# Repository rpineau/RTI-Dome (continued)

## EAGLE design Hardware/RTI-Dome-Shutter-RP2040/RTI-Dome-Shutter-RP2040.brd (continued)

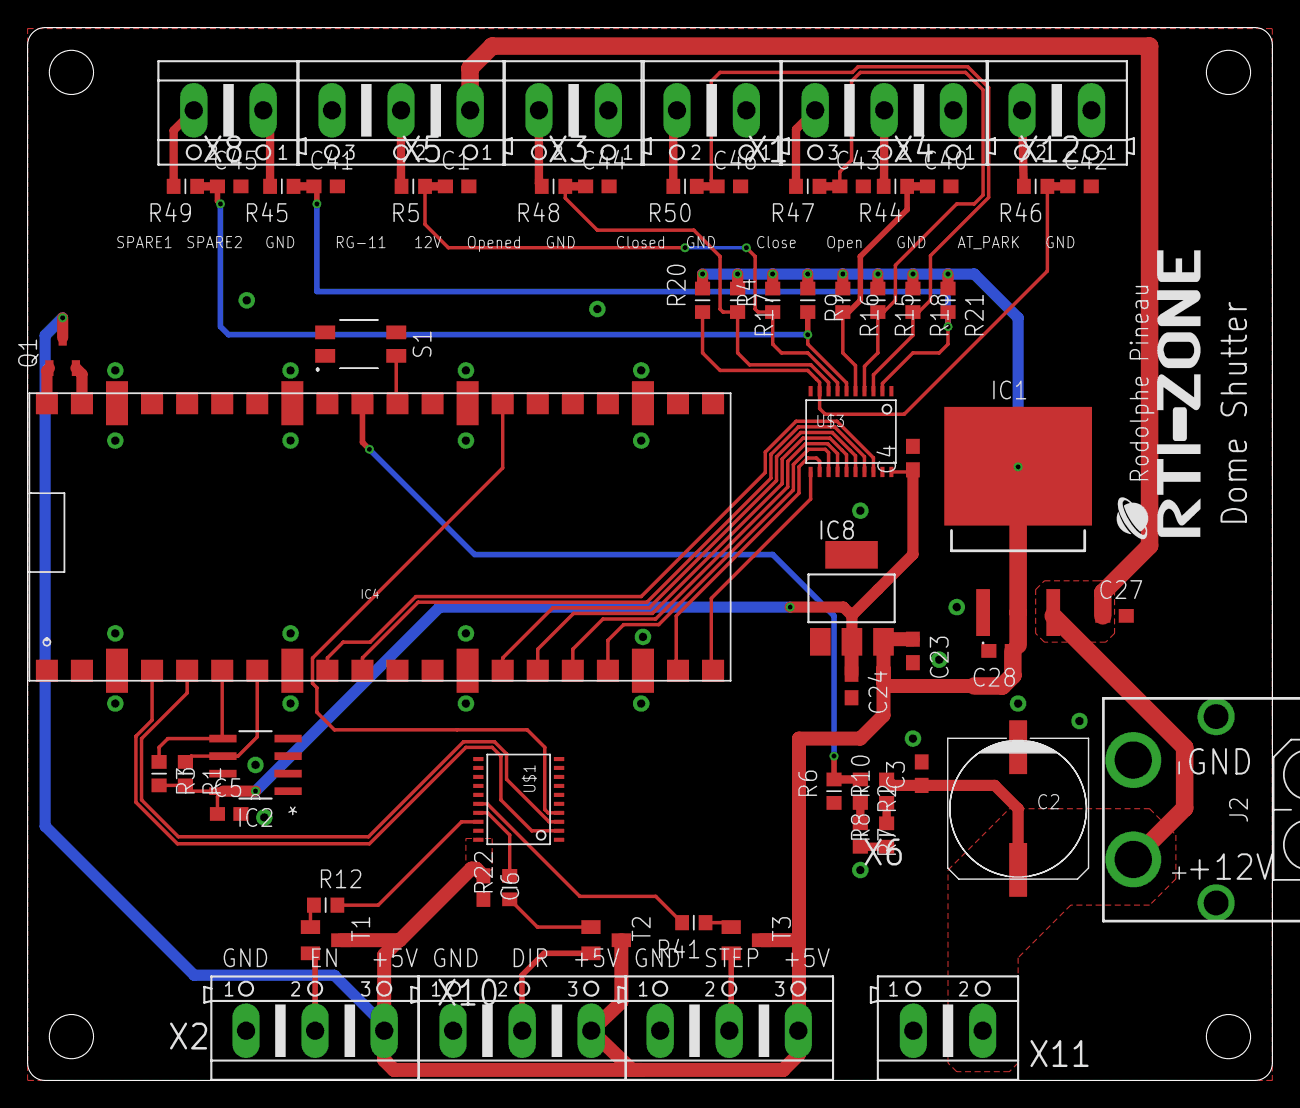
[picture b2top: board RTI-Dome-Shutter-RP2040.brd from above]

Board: 2 copper layers, 90.2 x 76.3 mm, 66 parts (0 on the bottom side), 49 nets.

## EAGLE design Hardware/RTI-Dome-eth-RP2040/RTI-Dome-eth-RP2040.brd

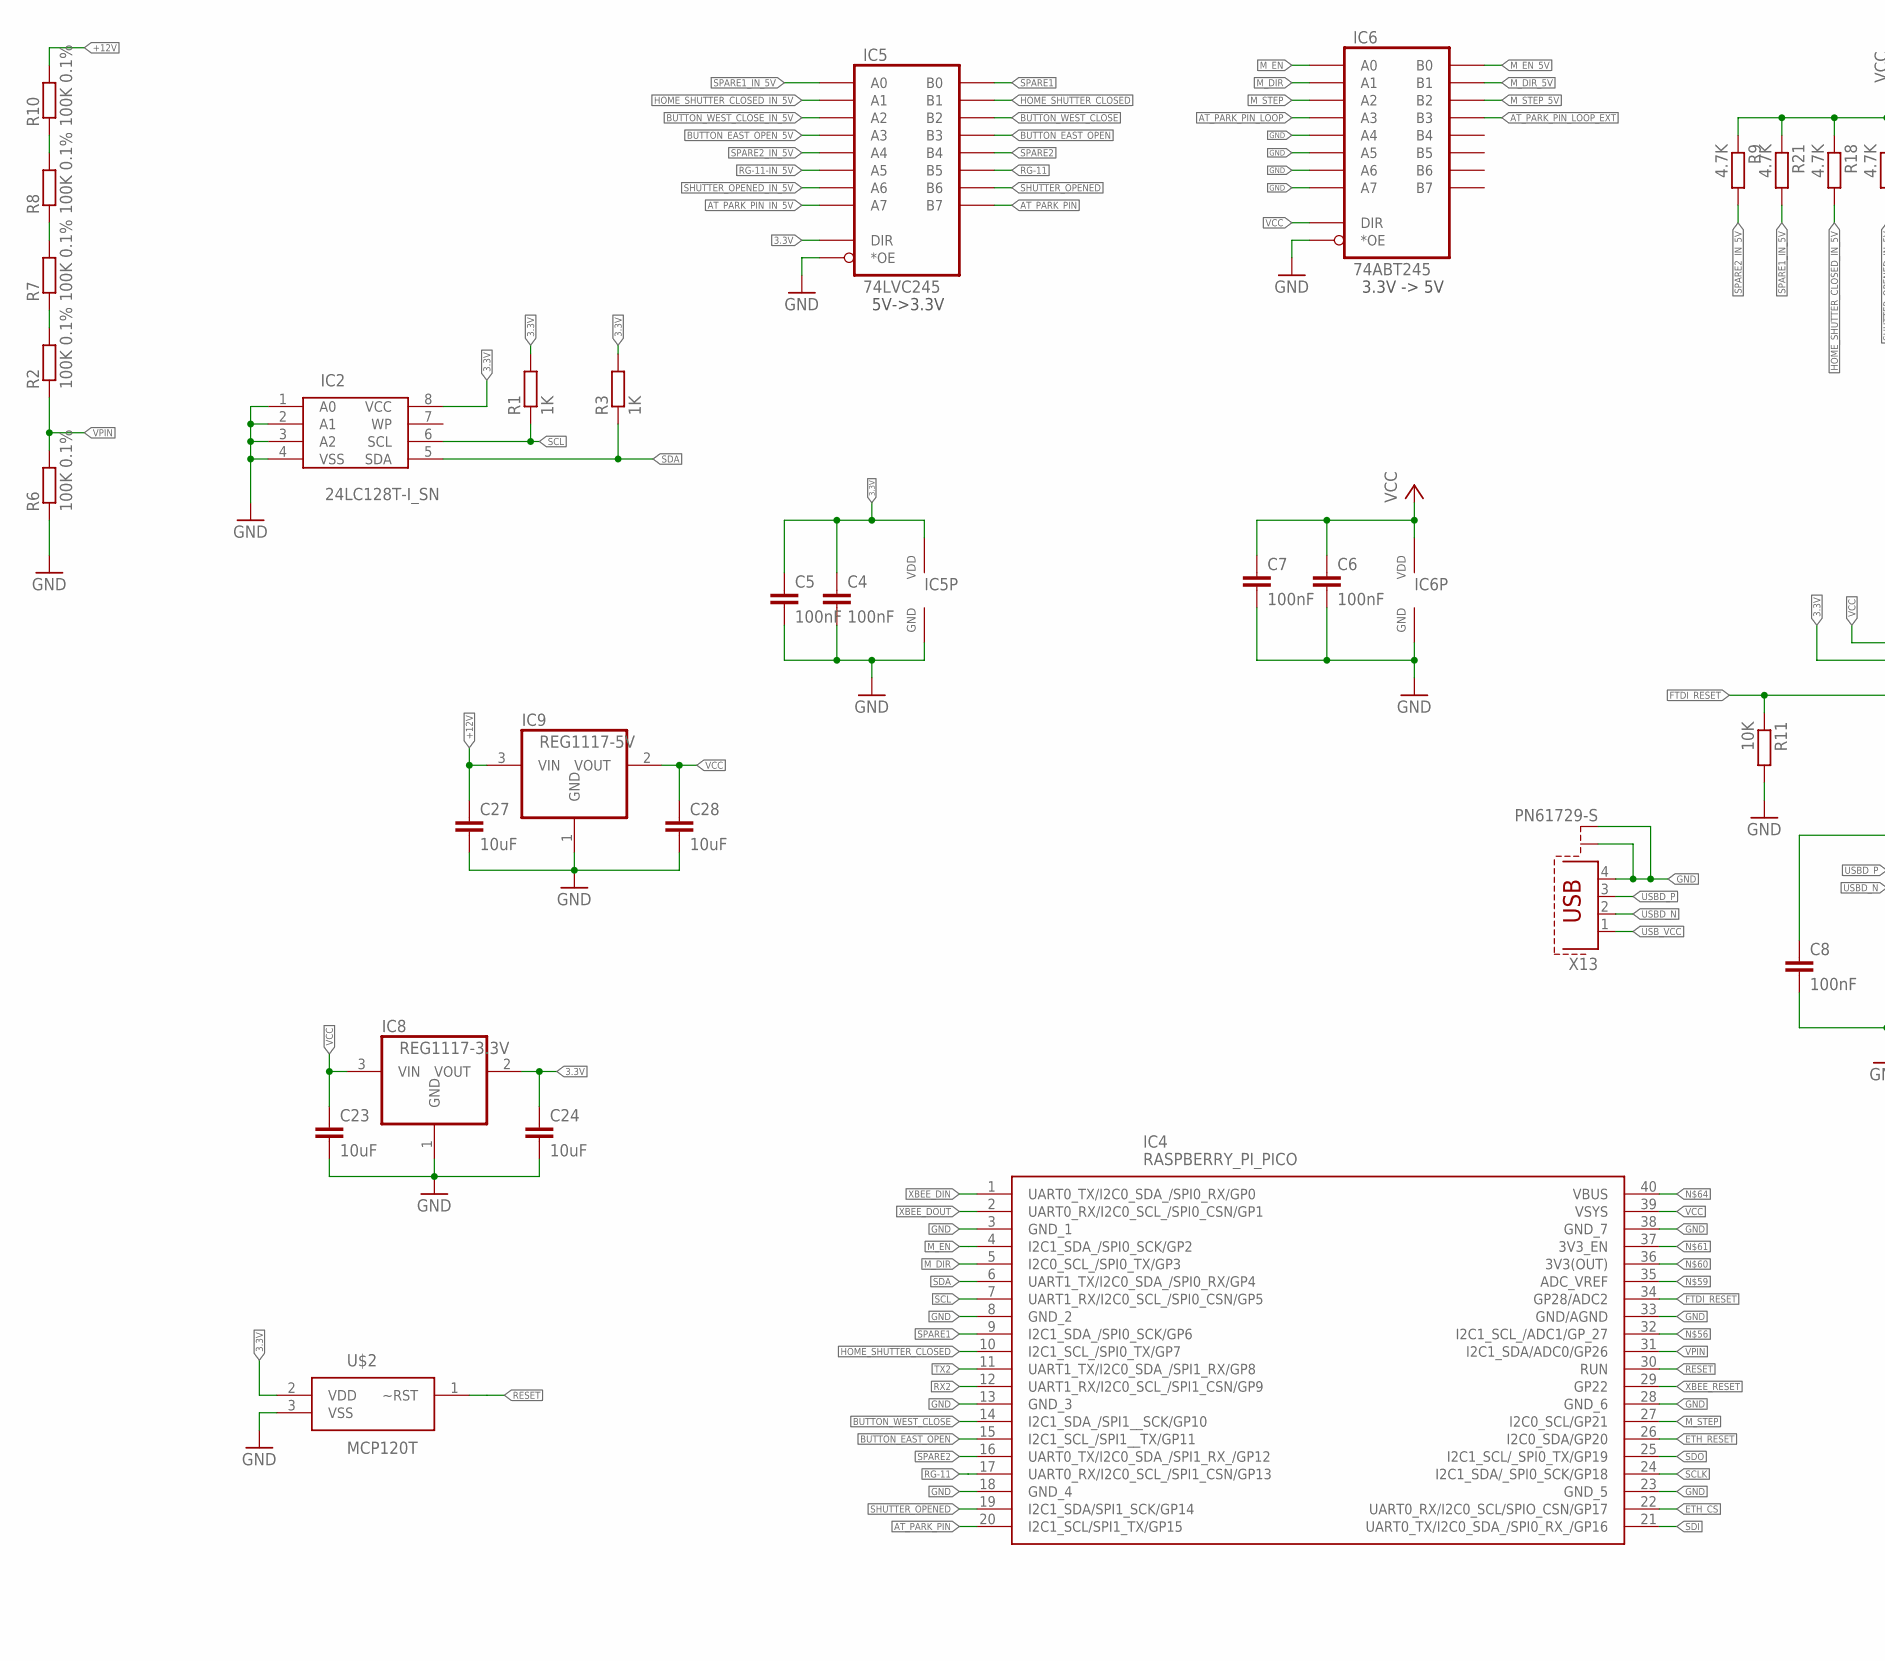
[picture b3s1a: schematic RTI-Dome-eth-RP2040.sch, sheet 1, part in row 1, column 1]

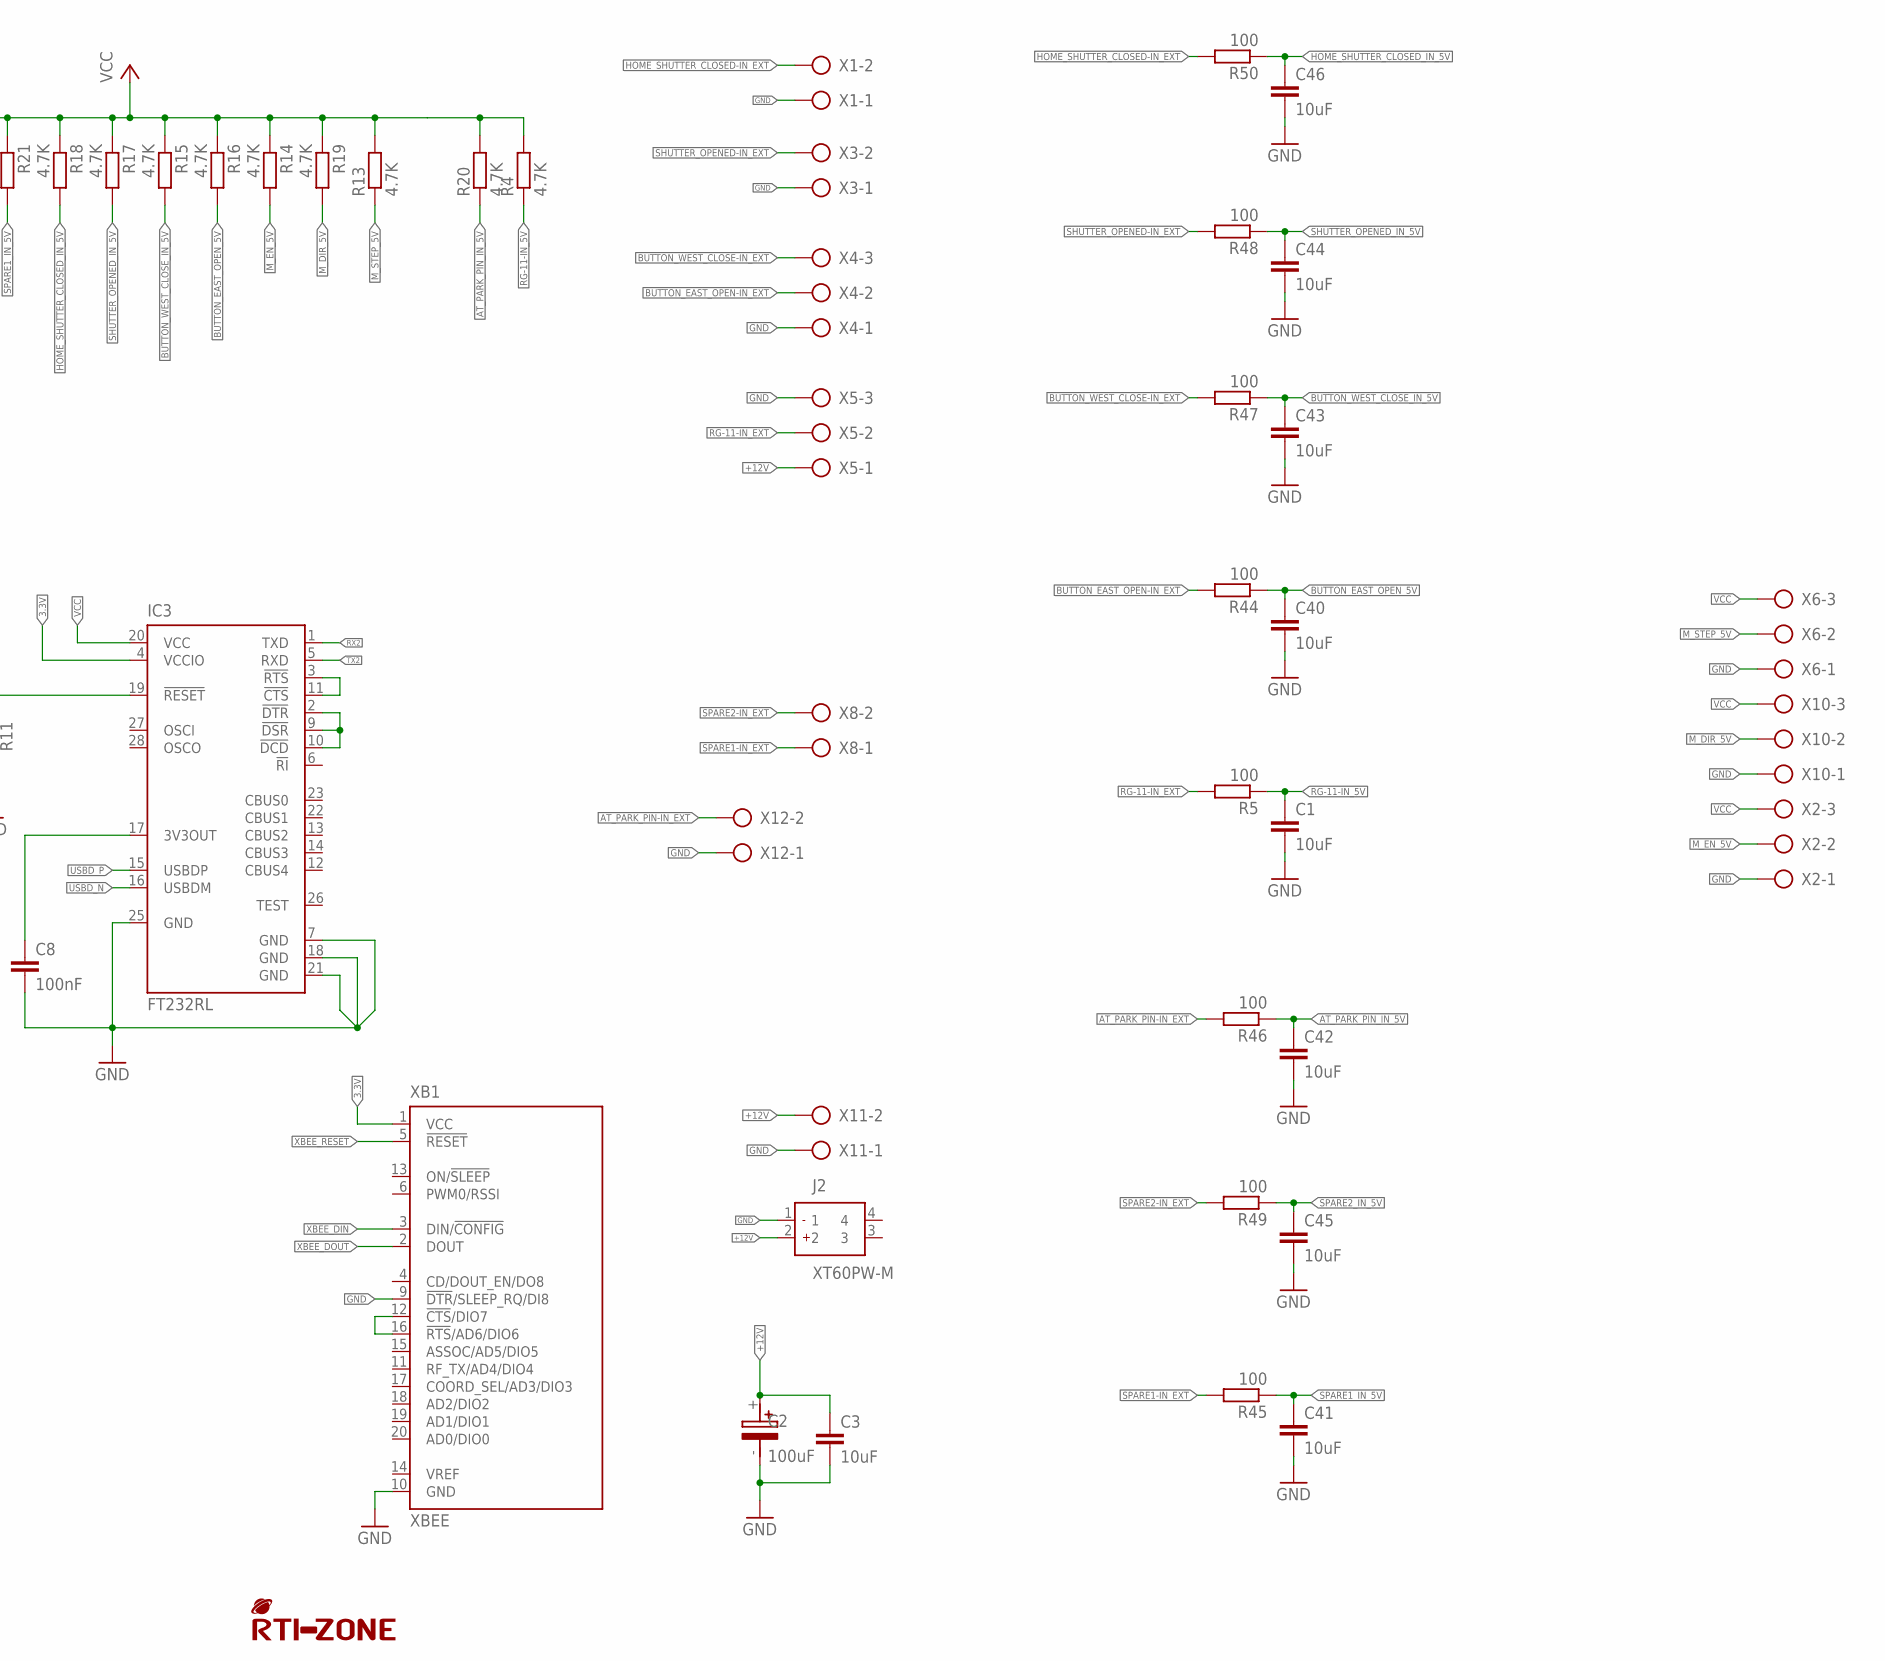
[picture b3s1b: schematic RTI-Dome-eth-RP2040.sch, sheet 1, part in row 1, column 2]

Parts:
C1, C3, C23, C24, C27, C28, C40, C41, C42, C43, C44, C45, C46: 10uF; C0805; MPN CC0805KKX5R8BB106
C2: 100uF; UD-10X10_NICHICON; MPN MAL215099804E3
C4, C5, C6, C7, C8: 100nF; C0805; MPN 0805YD104KAT2A
IC2: 24LC128T-I_SN; SOIC127P600X175-8N
IC3: FT232RL; SSOP28; MPN FT232RL-REEL
IC4: RASPBERRY_PI_PICO; RASPBERRYPIPICO; MANUFACTURER_PART_NUMBER SC0916; MOUSER_PART_NUMBER SC0915
IC5: 74LVC245; TSSOP20
IC6: 74ABT245; TSSOP20
IC8: REG1117-3.3V; SOT223; MPN REG1117-3.3/2K5
IC9: REG1117-5V; SOT223; MPN REG1117-3.3/2K5
J2: XT60PW-M; XT60PWM
R1, R3: 1K; R0805; MPN RT0805FRE071KL
R2, R6, R7, R8, R10: 100K 0.1%; R0805; MPN AT0805BRD07100KL
R4, R9, R13, R14, R15, R16, R17, R18, R19, R20, R21: 4.7K; R0805; MPN RT0805FRE074K7L
R5, R44, R45, R46, R47, R48, R49, R50: 100; R0805; MPN RT0805FRD07100RL
R11: 10K; R0805; MPN RT0805FRE0710KL
U$2: MCP120T; SOT95P237X112-3N; MPN MCP120T-270I/TT
U$4: RTI-LOGO_BIG; LOGO_BIG
X1, X3, X8, X11, X12: AK500/2; MPN 691101710002
X2, X6, X10: AK500/3
X4, X5: AK500/3; MPN 691101710003
X13: PN61729-S; MPN SS-52300-001
XB1: XBEE

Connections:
3.3V: C4.1, C5.1, C24.1, IC2.8 (VCC), IC3.4 (VCCIO), IC5.P$1 (DIR), IC5.P$20 (VDD), IC8.2 (VOUT), R1.2, R3.2, U$2.2 (VDD), XB1.1 (VCC); also elsewhere on the board
+12V: C2.+, C3.1, C27.1, IC9.3 (VIN), J2.2, R10.2, X5.1, X11.2
AT_PARK_PIN: IC4.20 (I2C1_SCL/SPI1_TX/GP15), IC5.P$11 (B7)
AT_PARK_PIN-IN_EXT: R46.2, X12.2
AT_PARK_PIN_IN_5V: C42.1, IC5.P$9 (A7), R20.1, R46.1
AT_PARK_PIN_LOOP: IC6.P$5 (A3)
AT_PARK_PIN_LOOP_EXT: IC6.P$15 (B3)
BUTTON_EAST_OPEN: IC4.15 (I2C1_SCL_/SPI1__TX/GP11), IC5.P$15 (B3)
BUTTON_EAST_OPEN-IN_EXT: R44.2, X4.2
BUTTON_EAST_OPEN_5V: C40.1, IC5.P$5 (A3), R16.2, R44.1
BUTTON_WEST_CLOSE: IC4.14 (I2C1_SDA_/SPI1__SCK/GP10), IC5.P$16 (B2)
BUTTON_WEST_CLOSE-IN_EXT: R47.2, X4.3
BUTTON_WEST_CLOSE_IN_5V: C43.1, IC5.P$4 (A2), R15.2, R47.1
DTR_DSR_DCD: IC3.2 (!DTR), IC3.9 (!DSR), IC3.10 (!DCD)
ETH_CS: IC4.22 (UART0_RX/I2C0_SCL/SPIO_CSN/GP17); also elsewhere on the board
ETH_RESET: IC4.26 (I2C0_SDA/GP20); also elsewhere on the board
FTDI_RESET: IC3.19 (!RESET), IC4.34 (GP28/ADC2), R11.1
GND: C1.2, C2.-, C3.2, C4.2, C5.2, C6.2, C7.2, C8.2, C23.2, C24.2, C27.2, C28.2, C40.2, C41.2, C42.2, C43.2, C44.2, C45.2, C46.2, IC2.1 (A0), IC2.2 (A1), IC2.3 (A2), IC2.4 (VSS), IC3.7 (GND), IC3.18 (GND), IC3.21 (GND), IC3.25 (GND), IC4.3 (GND_1), IC4.8 (GND_2), IC4.13 (GND_3), IC4.18 (GND_4), IC4.23 (GND_5), IC4.28 (GND_6), IC4.33 (GND/AGND), IC4.38 (GND_7), IC5.P$10 (GND), IC5.P$19 (*OE), IC6.P$6 (A4), IC6.P$7 (A5), IC6.P$8 (A6), IC6.P$9 (A7), IC6.P$10 (GND), IC6.P$19 (*OE), IC8.1 (GND), IC9.1 (GND), J2.1, R6.1, R11.2, U$2.3 (VSS), X1.1, X2.1, X3.1, X4.1, X5.3, X6.1, X10.1, X11.1, X12.1, X13.4, X13.S1, X13.S2, XB1.9 (!DTR!/SLEEP_RQ/DI8), XB1.10 (GND); also elsewhere on the board
HOME_SHUTTER_CLOSED: IC4.10 (I2C1_SCL_/SPI0_TX/GP7), IC5.P$17 (B1)
HOME_SHUTTER_CLOSED-IN_EXT: R50.2, X1.2
HOME_SHUTTER_CLOSED_IN_5V: C46.1, IC5.P$3 (A1), R18.2, R50.1
M_DIR: IC4.5 (I2C0_SCL_/SPI0_TX/GP3), IC6.P$3 (A1)
M_DIR_5V: IC6.P$17 (B1), R19.2, X10.2
M_EN: IC4.4 (I2C1_SDA_/SPI0_SCK/GP2), IC6.P$2 (A0)
M_EN_5V: IC6.P$18 (B0), R14.2, X2.2
M_STEP: IC4.27 (I2C0_SCL/GP21), IC6.P$4 (A2)
M_STEP_5V: IC6.P$16 (B2), R13.1, X6.2
unnamed: R7.2, R8.1
unnamed: R8.2, R10.1
unnamed: R2.2, R7.1
unnamed: C8.1, IC3.17 (3V3OUT)
unnamed: XB1.12 (!CTS!/DIO7), XB1.16 (!RTS!/AD6/DIO6)
RESET: IC4.30 (RUN), U$2.1 (~RST)
RG-11: IC4.17 (UART0_RX/I2C0_SCL_/SPI1_CSN/GP13), IC5.P$13 (B5)
RG-11-IN_5V: C1.1, IC5.P$7 (A5), R4.1, R5.1
RG-11-IN_EXT: R5.2, X5.2
RTS_CTS: IC3.3 (!RTS), IC3.11 (!CTS)
RX2: IC3.1 (TXD), IC4.12 (UART1_RX/I2C0_SCL_/SPI1_CSN/GP9)
SCL: IC2.6 (SCL), IC4.7 (UART1_RX/I2C0_SCL_/SPI0_CSN/GP5), R1.1
SCLK: IC4.24 (I2C1_SDA/_SPI0_SCK/GP18); also elsewhere on the board
SDA: IC2.5 (SDA), IC4.6 (UART1_TX/I2C0_SDA_/SPI0_RX/GP4), R3.1
SDI: IC4.21 (UART0_TX/I2C0_SDA_/SPI0_RX_/GP16); also elsewhere on the board
SDO: IC4.25 (I2C1_SCL/_SPI0_TX/GP19); also elsewhere on the board
SHUTTER_OPENED: IC4.19 (I2C1_SDA/SPI1_SCK/GP14), IC5.P$12 (B6)
SHUTTER_OPENED-IN_EXT: R48.2, X3.2
SHUTTER_OPENED_IN_5V: C44.1, IC5.P$8 (A6), R17.2, R48.1
SPARE1: IC4.9 (I2C1_SDA_/SPI0_SCK/GP6), IC5.P$18 (B0)
SPARE1-IN_EXT: R45.2, X8.1
SPARE1_IN_5V: C41.1, IC5.P$2 (A0), R21.2, R45.1
SPARE2: IC4.16 (UART0_TX/I2C0_SDA_/SPI1_RX_/GP12), IC5.P$14 (B4)
SPARE2-IN_EXT: R49.2, X8.2
SPARE2_IN_5V: C45.1, IC5.P$6 (A4), R9.2, R49.1
TX2: IC3.5 (RXD), IC4.11 (UART1_TX/I2C0_SDA_/SPI1_RX/GP8)
USBD_N: IC3.16 (USBDM), X13.2
USBD_P: IC3.15 (USBDP), X13.3
USB_VCC: X13.1
VCC: C6.1, C7.1, C23.1, C28.1, IC3.20 (VCC), IC4.39 (VSYS), IC6.P$1 (DIR), IC6.P$20 (VDD), IC8.3 (VIN), IC9.2 (VOUT), R4.2, R9.1, R13.2, R14.1, R15.1, R16.1, R17.1, R18.1, R19.1, R20.2, R21.1, X2.3, X6.3, X10.3
VPIN: IC4.31 (I2C1_SDA/ADC0/GP26), R2.1, R6.2
XBEE_DIN: IC4.1 (UART0_TX/I2C0_SDA_/SPI0_RX/GP0), XB1.3 (DIN/!CONFIG)
XBEE_DOUT: IC4.2 (UART0_RX/I2C0_SCL_/SPI0_CSN/GP1), XB1.2 (DOUT)
XBEE_RESET: IC4.29 (GP22), XB1.5 (!RESET)

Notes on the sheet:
5V->3.3V
3.3V -> 5V

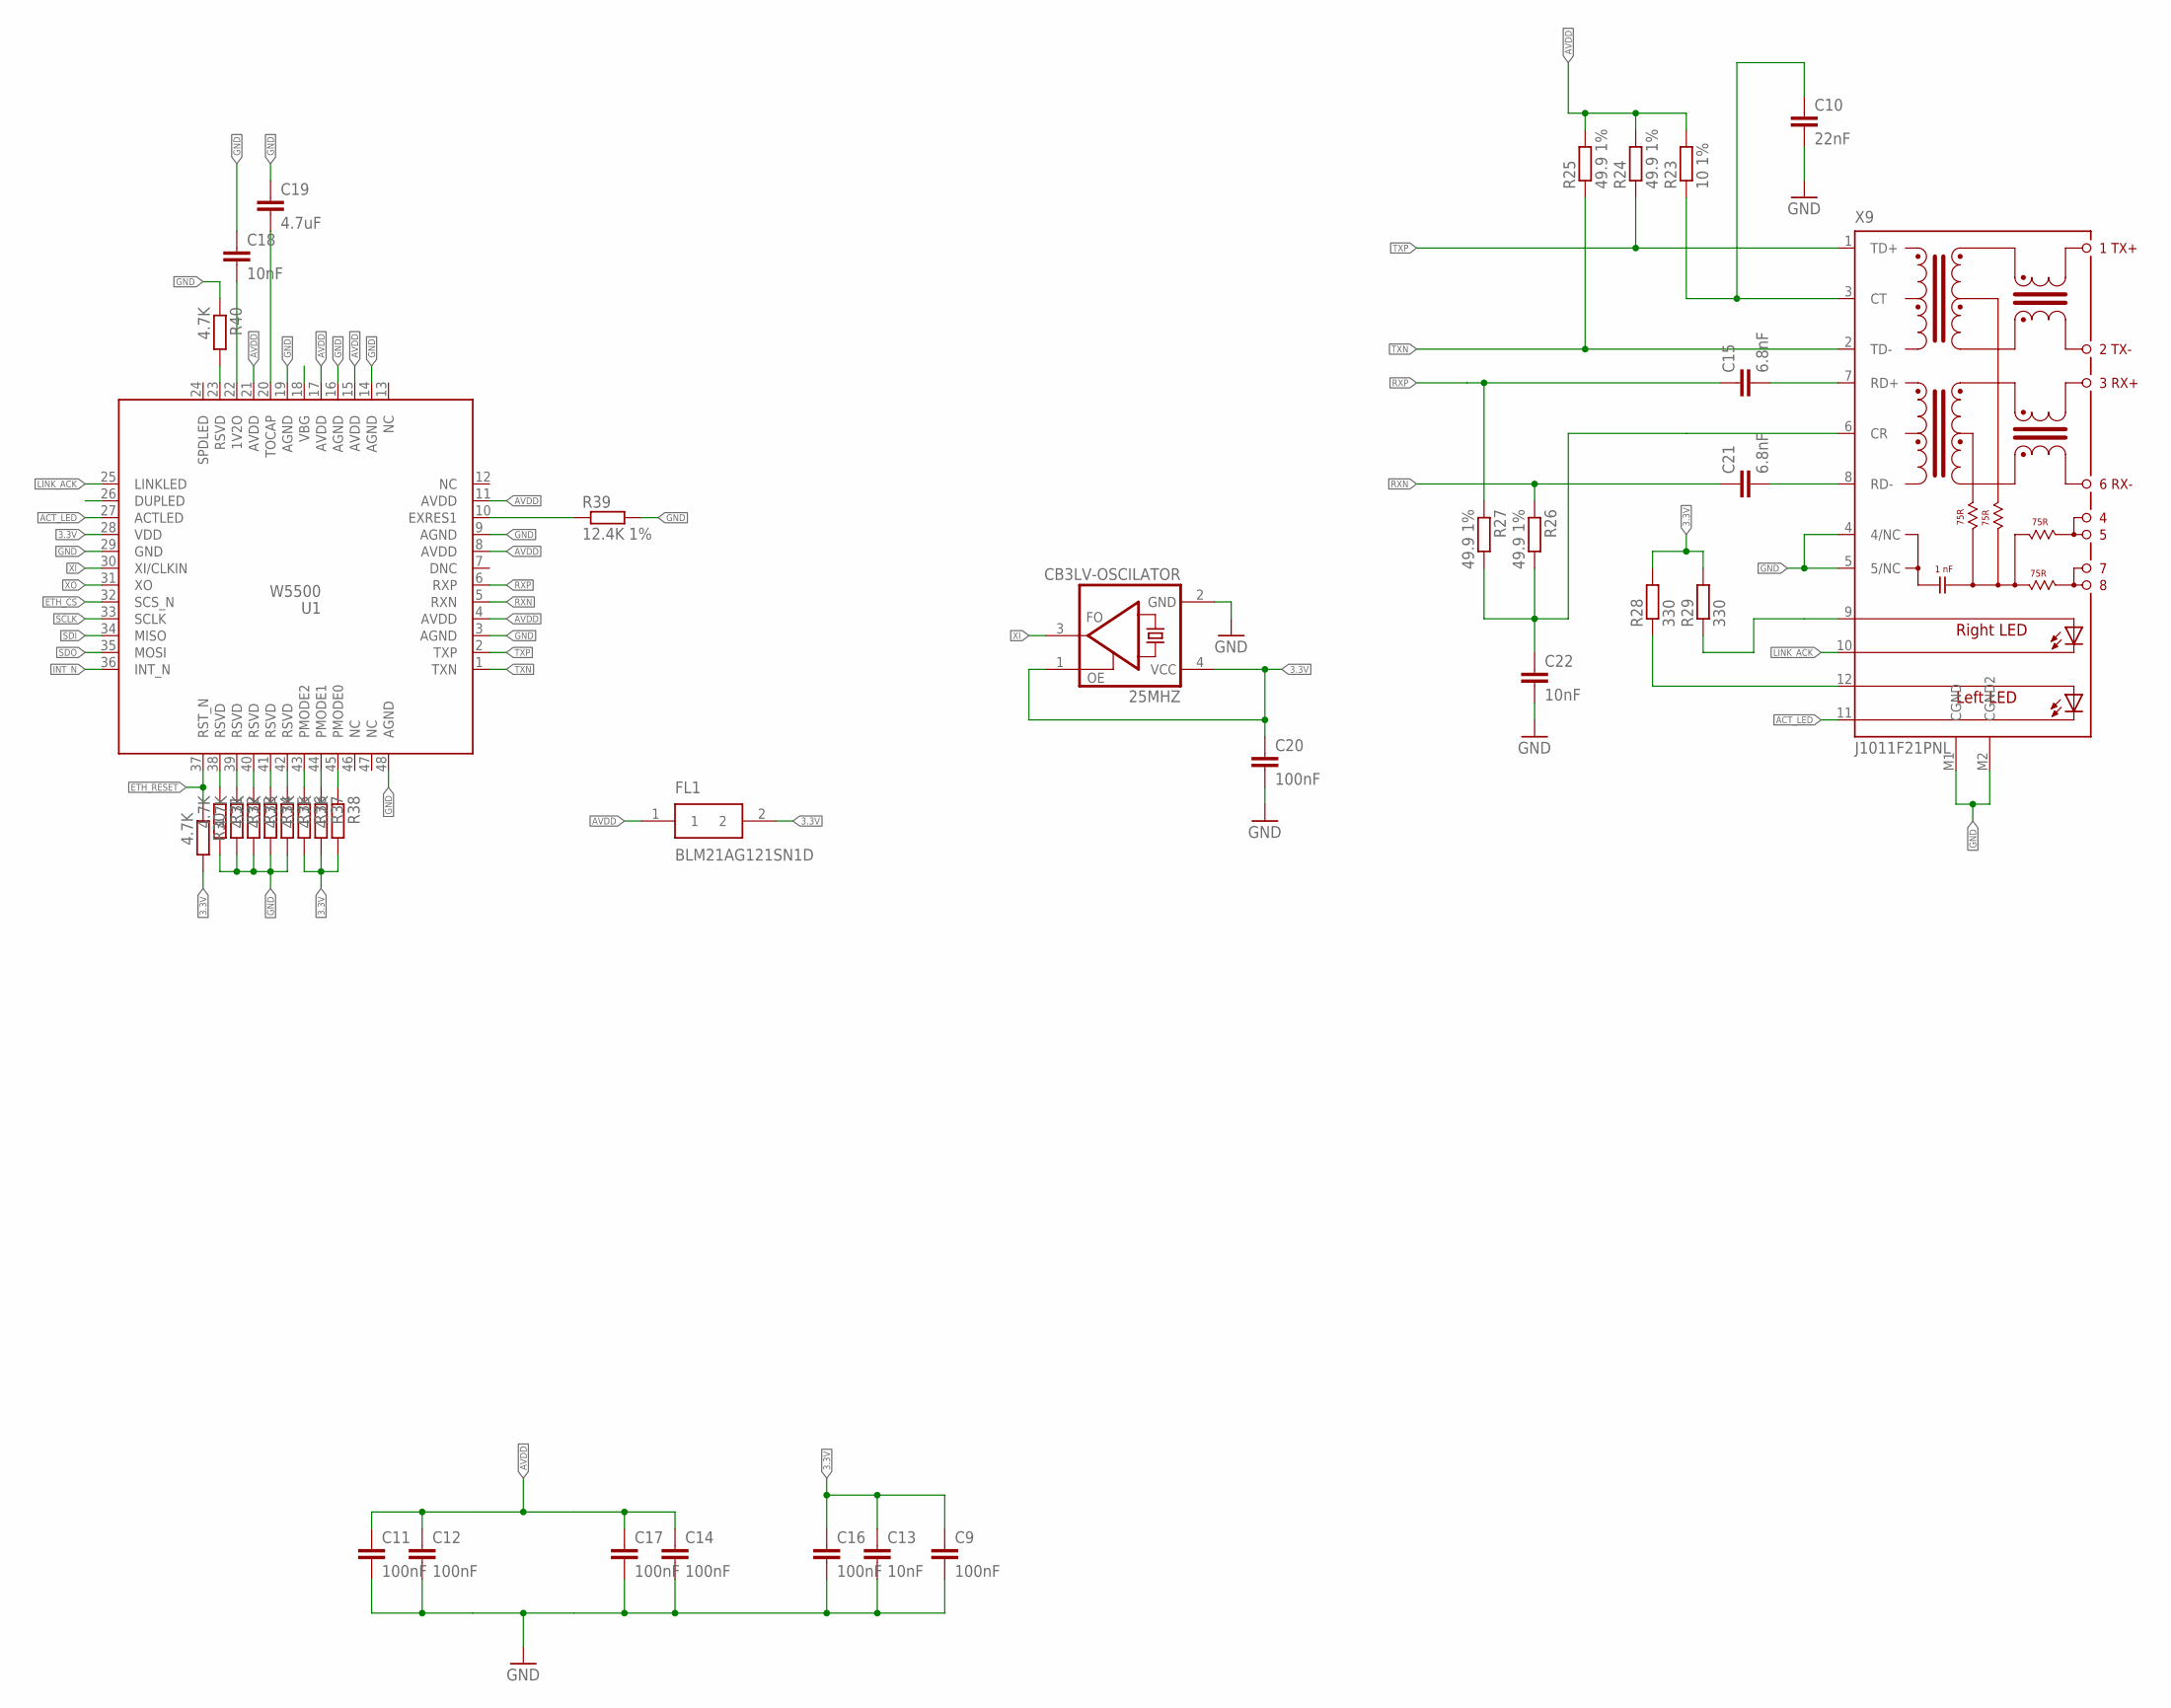
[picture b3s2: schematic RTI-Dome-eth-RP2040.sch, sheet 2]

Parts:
25MHZ: CB3LV-OSCILATOR; SMD-7050_4P; MPN CB3LV-3I-25M0000
C9, C11, C12, C14, C16, C17, C20: 100nF; C0805; MPN 0805YD104KAT2A
C10: 22nF; C0805; MPN CC0805JRX7R8BB223
C13, C18, C22: 10nF; C0805; MPN CC0805KRX7R9BB103
C15, C21: 6.8nF; C0805; MPN C0805C682F4HACTU
C19: 4.7uF; C0805; MPN C0805C475J3RACTU
FL1: BLM21AG121SN1D; L0805; MPN BLM21AG121SN1D
R23: 10 1%; R0805; MPN RT0805FRE1310RL
R24, R25, R26, R27: 49.9 1%; R0805; MPN RC0805FR-0749R9L
R28, R29: 330; R0805; MPN RC0805JR-07330RL
R30, R31, R32, R33, R34, R35, R36, R37, R38, R40: 4.7K; R0805; MPN RT0805FRE074K7L
R39: 12.4K 1%; R0805; MPN RC0805FR-0712K4L
U1: W5500; LQFP48; MPN W5500
X9: J1011F21PNL; MPN J1011F21PNL

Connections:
3.3V: 25MHZ.1 (OE), 25MHZ.4 (VDD), C9.1, C13.1, C16.1, C20.1, FL1.2, R28.2, R29.2, R30.2, R36.2, R37.2, R38.2, U1.28 (VDD); also elsewhere on the board
ACT_LED: U1.27 (ACTLED), X9.11 (C-L)
AVDD: C11.1, C12.1, C14.1, C17.1, FL1.1, R23.2, R24.2, R25.2, U1.4 (AVDD), U1.8 (AVDD), U1.11 (AVDD), U1.15 (AVDD), U1.17 (AVDD), U1.21 (AVDD)
ETH_CS: U1.32 (SCS_N); also elsewhere on the board
ETH_RESET: R30.1, U1.37 (RST_N); also elsewhere on the board
GND: 25MHZ.2 (GND), C9.2, C10.2, C11.2, C12.2, C13.2, C14.2, C16.2, C17.2, C18.1, C19.1, C20.2, C22.2, R31.2, R32.2, R33.2, R34.2, R35.2, R39.2, R40.1, U1.3 (AGND), U1.9 (AGND), U1.14 (AGND), U1.16 (AGND), U1.19 (AGND), U1.29 (GND), U1.48 (AGND), X9.4 (4/NC), X9.5 (5/NC), X9.M1 (CGND), X9.M2 (CGND2); also elsewhere on the board
INT_N: U1.36 (INT_N)
LINK_ACK: U1.25 (LINKLED), X9.10 (C-R)
unnamed: C22.1, R26.2, R27.2, X9.6 (CR)
unnamed: R29.1, X9.9 (A-R)
unnamed: R28.1, X9.12 (AL)
unnamed: C15.2, X9.7 (RD+)
unnamed: C21.2, X9.8 (RD-)
unnamed: C10.1, R23.1, X9.3 (CT)
unnamed: R31.1, U1.38 (RSVD)
unnamed: R32.1, U1.39 (RSVD)
unnamed: R33.1, U1.40 (RSVD)
unnamed: R34.1, U1.41 (RSVD)
unnamed: R35.1, U1.42 (RSVD)
unnamed: R36.1, U1.43 (PMODE2)
unnamed: R37.1, U1.44 (PMODE1)
unnamed: R38.1, U1.45 (PMODE0)
unnamed: C19.2, U1.20 (TOCAP)
unnamed: C18.2, U1.22 (1V2O)
unnamed: R39.1, U1.10 (EXRES1)
unnamed: R40.2, U1.23 (RSVD)
RXN: C21.1, R26.1, U1.5 (RXN)
RXP: C15.1, R27.1, U1.6 (RXP)
SCLK: U1.33 (SCLK); also elsewhere on the board
SDI: U1.34 (MISO); also elsewhere on the board
SDO: U1.35 (MOSI); also elsewhere on the board
TXN: R25.1, U1.1 (TXN), X9.2 (TD-)
TXP: R24.1, U1.2 (TXP), X9.1 (TD+)
XI: 25MHZ.3 (FO), U1.30 (XI/CLKIN)
XO: U1.31 (XO)

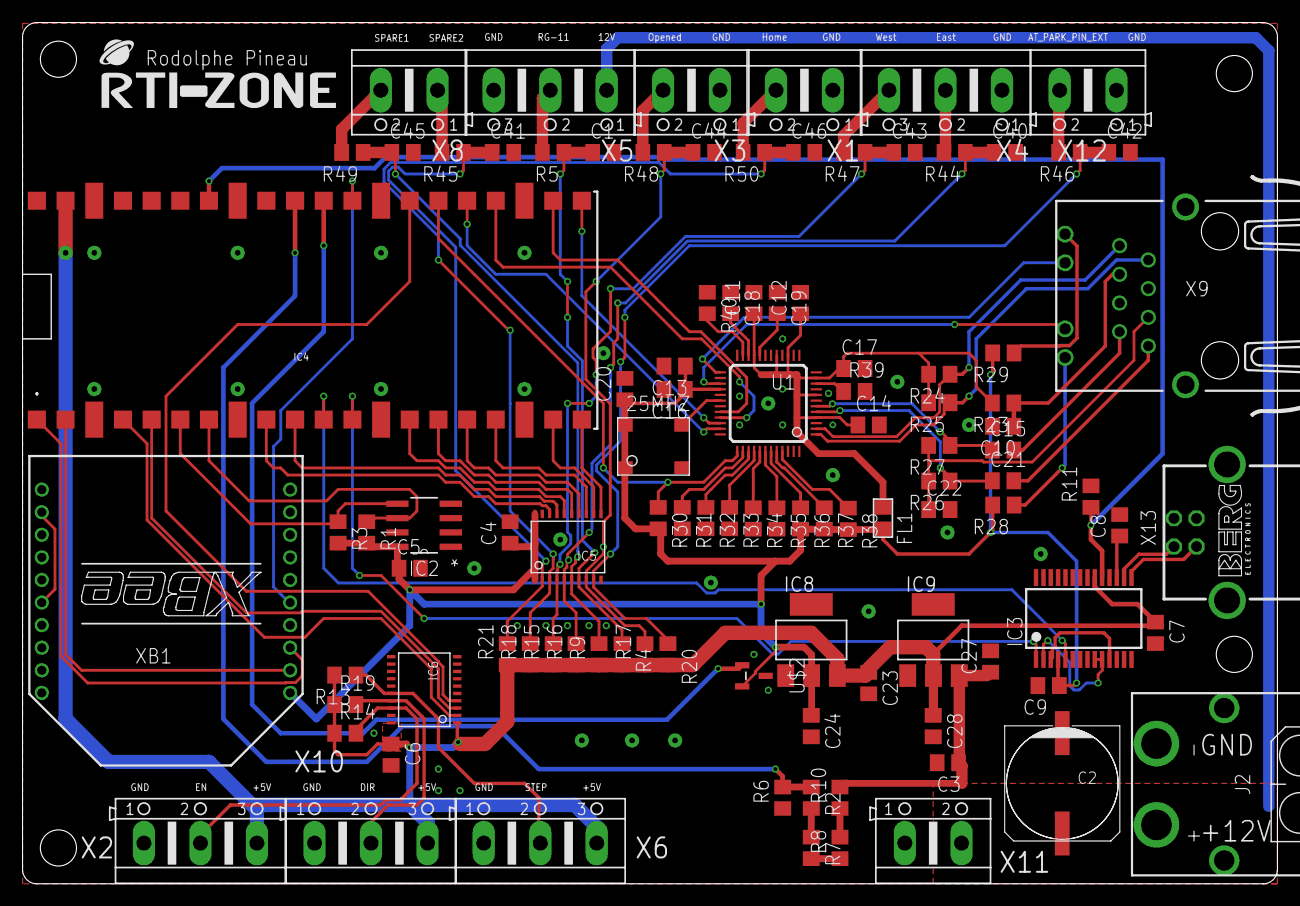
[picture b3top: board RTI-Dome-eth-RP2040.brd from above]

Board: 2 copper layers, 111.1 x 76.3 mm, 104 parts (0 on the bottom side), 84 nets.
